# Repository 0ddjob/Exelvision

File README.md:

# Exelvision EXL100
Hardware projects and other info for the French Exelvision EXL100 computer.<br>
It has the following main ICs:
- Texas Instruments TMS4408 ... 8k x 4bit giving 32KBytes of shared VRAM
- NEC D4016 ... 2KByte SRAM for CPU RAM
- Texas Instruments TAL004 ... Gate Array
- Texas Instruments L30002N ... TMS 7220 CPU
- Texas Instruments C34802N ... TMS 7041 peripheral co-processor
- Texas Instruments TMP5220CNL ... TMS 5220 speech synthesiser
- Texas Instruments TMX3556NS ... TMS 3556 video display processor (VDP)

The ROM cartridge connector is a BURNDY PWBH14DER1A-1 which I can't find any info on - it's a 2x14 design.<br>

## YouTube Videos
- [Part 1: First Look](https://youtu.be/5-ew3FQ9LnI)
- [Part 2: Cartridge Pinout](https://youtu.be/ktFMq2L3tBw)
- [Simple Kicad For Simple Vintage Computer Hobbyists: Part 4 (ROM Cartridge Design)](https://youtu.be/4mT13-wXdjI)
- [Part 3: DIY Cartridges](https://youtu.be/ecWkOvze2gc)

## [EXLROM - Multi-ROM cartridge](/EXLROM/)
The EXL100 could accept ROM cartridges from 8KByte to 32KByte in size, including BASIC.  By using a 4Mbit ROM (27C040) we can fit all known ROMs onto one cartridge.  How exciting.<br>
I've designed two versions: a simple 256kbit version that will hold a single 32KByte ROM (like the olden days) and the 4Mbit version that will hold up to 16 32KByte ROMs.<br>
### Status
- 1-Apr-2025:  Pending test fabrication 
- 10-Apr-2025: Test PCBs arrived & verified! Refer YouTube video.

## Partial TAL004 Gate Array Pinout
From cartridge pinout investigation ... <br>

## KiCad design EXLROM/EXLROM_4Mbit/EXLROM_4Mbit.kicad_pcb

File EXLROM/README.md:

# EXLROM Multi-ROM Cartridge
## Summary
The Exelvision EXL100 (and Exeltel) cartridge port pinout is below - the B-side face up and A-side face down when the cartridge is inserted.<br>
The pinout was determined from the 32KByte Tennis cartridge.  The A1 pin was not connected in this cartridge but is connected to pin 40 of the TAL004 gate array ... perhaps a 2nd ROM select line?<br>
```
A1 = ROMCS2(?)  B1 = ROMCS1
A2 = A13        B2 = A14
A3 = A11        B3 = A12
A4 = A9         B4 = A10
A5 = A7         B5 = A8
A6 = A5         B6 = A6
A7 = GND        B7 = A4
A8 = N/C        B8 = +5V
A9 = A3         B9 = A2
A10 = A1        B10 = A0
A11 = D7        B11 = D6
A12 = D5        B12 = D4
A13 = D3        B13 = D2
A14 = D1        B14 = D0
```
## [Simple Single ROM Version](/EXLROM/EXLROM_256Kbit/)
This version takes a 32KByte 27C256 EPROM that will fit a single 32KByte ROM.  The smaller 8KByte and 16KByte ROMs will just have empty space.<br>

## [Multi-ROM](/EXLROM/EXLROM_4Mbit/)
This version should fit all known Exelvision ROMs.<br>

## Bank Selection
Using a 4MBit EPROM allows us to fit 16 32KByte ROMs selectable via four dip switches that determine the value of the A15 to A18 address lines.  A single ROM can be created by concatenating 32KByte ROMs into one file - very simply done in Linux or Windows via command line.  Smaller ROMs (8KByte and 16KByte) can be duplcated (i.e. four concatenated copies of the 8KByte ROM) to bring their size up to 32KBytes.
```
AAAA 
1111
8765 Bank  ROM Address Range
---- ----  -----------------
0000    0  0x00000-0x07FFF
0001    1  0x08000-0x0FFFF
0010    2  0x10000-0x17FFF
0011    3  0x18000-0x1FFFF
0100    4  0x20000-0x27FFF
0101    5  0x28000-0x2FFFF
0110    6  0x30000-0x37FFF
0111    7  0x38000-0x3FFFF
1000    8  0x40000-0x47FFF
1001    9  0x48000-0x4FFFF
1010   10  0x50000-0x57FFF
1011   11  0x58000-0x5FFFF
1100   12  0x60000-0x67FFF
1101   13  0x68000-0x6FFFF
1110   14  0x70000-0x77FFF
1111   15  0x78000-0x7FFFF
```
## Cartridge Pinout
The B-side that faces up when inserted.  Pins are numbered B1 on the right to B14 on left.<br>

The A-side that faces down when inserted.  Pins are numbered A1 on the right and A14 on the left.<br>

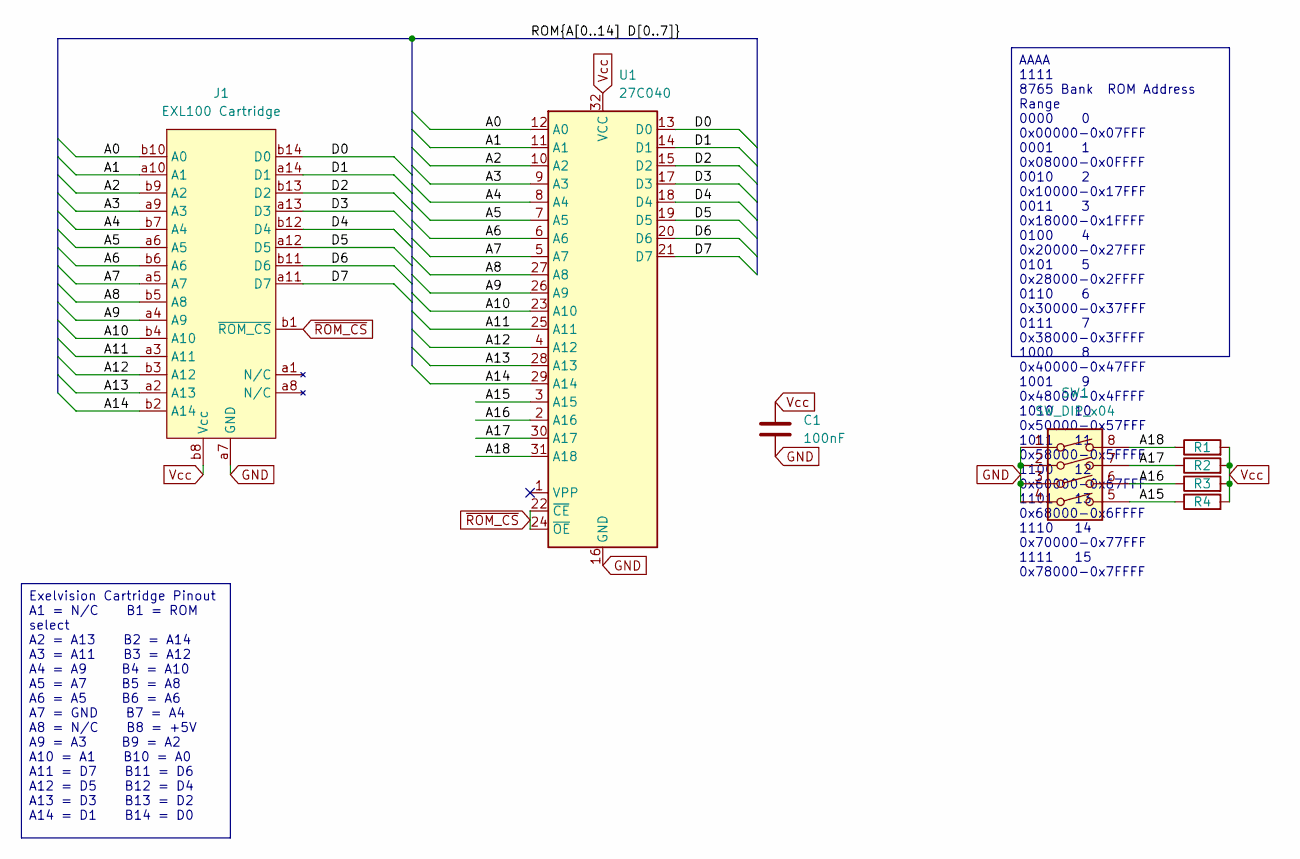
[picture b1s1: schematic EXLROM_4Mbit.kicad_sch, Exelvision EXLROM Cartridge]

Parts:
C1: 100nF; C_Disc_D3.0mm_W2.0mm_P2.50mm
J1: EXL100 Cartridge; EXL100_Cartridge
R1, R2, R3, R4: 10KΩ; R_Axial_DIN0207_L6.3mm_D2.5mm_P10.16mm_Horizontal
SW1: SW_DIP_x04; SW_DIP_SPSTx04_Slide_9.78x12.34mm_W7.62mm_P2.54mm
U1: 27C040; DIP-32_W15.24mm_Socket

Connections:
/A0: J1.b10 (A0), U1.12 (A0)
/A1: J1.a10 (A1), U1.11 (A1)
/A2: J1.b9 (A2), U1.10 (A2)
/A3: J1.a9 (A3), U1.9 (A3)
/A4: J1.b7 (A4), U1.8 (A4)
/A5: J1.a6 (A5), U1.7 (A5)
/A6: J1.b6 (A6), U1.6 (A6)
/A7: J1.a5 (A7), U1.5 (A7)
/A8: J1.b5 (A8), U1.27 (A8)
/A9: J1.a4 (A9), U1.26 (A9)
/A10: J1.b4 (A10), U1.23 (A10)
/A11: J1.a3 (A11), U1.25 (A11)
/A12: J1.b3 (A12), U1.4 (A12)
/A13: J1.a2 (A13), U1.28 (A13)
/A14: J1.b2 (A14), U1.29 (A14)
/A15: R4.1, SW1.5, U1.3 (A15)
/A16: R3.1, SW1.6, U1.2 (A16)
/A17: R2.1, SW1.7, U1.30 (A17)
/A18: R1.1, SW1.8, U1.31 (A18)
/D0: J1.b14 (D0), U1.13 (D0)
/D1: J1.a14 (D1), U1.14 (D1)
/D2: J1.b13 (D2), U1.15 (D2)
/D3: J1.a13 (D3), U1.17 (D3)
/D4: J1.b12 (D4), U1.18 (D4)
/D5: J1.a12 (D5), U1.19 (D5)
/D6: J1.b11 (D6), U1.20 (D6)
/D7: J1.a11 (D7), U1.21 (D7)
GND: C1.2, J1.a7 (GND), SW1.1, SW1.2, SW1.3, SW1.4, U1.16 (GND)
Vcc: C1.1, J1.b8 (Vcc), R1.2, R2.2, R3.2, R4.2, U1.32 (VCC)
~ROM_CS: J1.b1 (~ROM_CS), U1.22 (~CE), U1.24 (~OE)

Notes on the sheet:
Exelvision Cartridge Pinout A1 = N/C B1 = ROM select A2 = A13 B2 = A14 A3 = A11 B3 = A12 A4 = A9 B4 = A10 A5 = A7 B5 = A8 A6 = A5 B6 = A6 A7 = GND B7 = A4 A8 = N/C B8 = +5V A9 = A3 B9 = A2 A10 = A1 B10 = A0 A11 = D7 B11 = D6 A12 = D5 B12 = D4 A13 = D3 B13 = D2 A14 = D1 B14 = D0
AAAA 1111 8765 Bank ROM Address Range 0000 0 0x00000-0x07FFF 0001 1 0x08000-0x0FFFF 0010 2 0x10000-0x17FFF 0011 3 0x18000-0x1FFFF 0100 4 0x20000-0x27FFF 0101 5 0x28000-0x2FFFF 0110 6 0x30000-0x37FFF 0111 7 0x38000-0x3FFFF 1000 8 0x40000-0x47FFF 1001 9 0x48000-0x4FFFF 1010 10 0x50000-0x57FFF 1011 11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

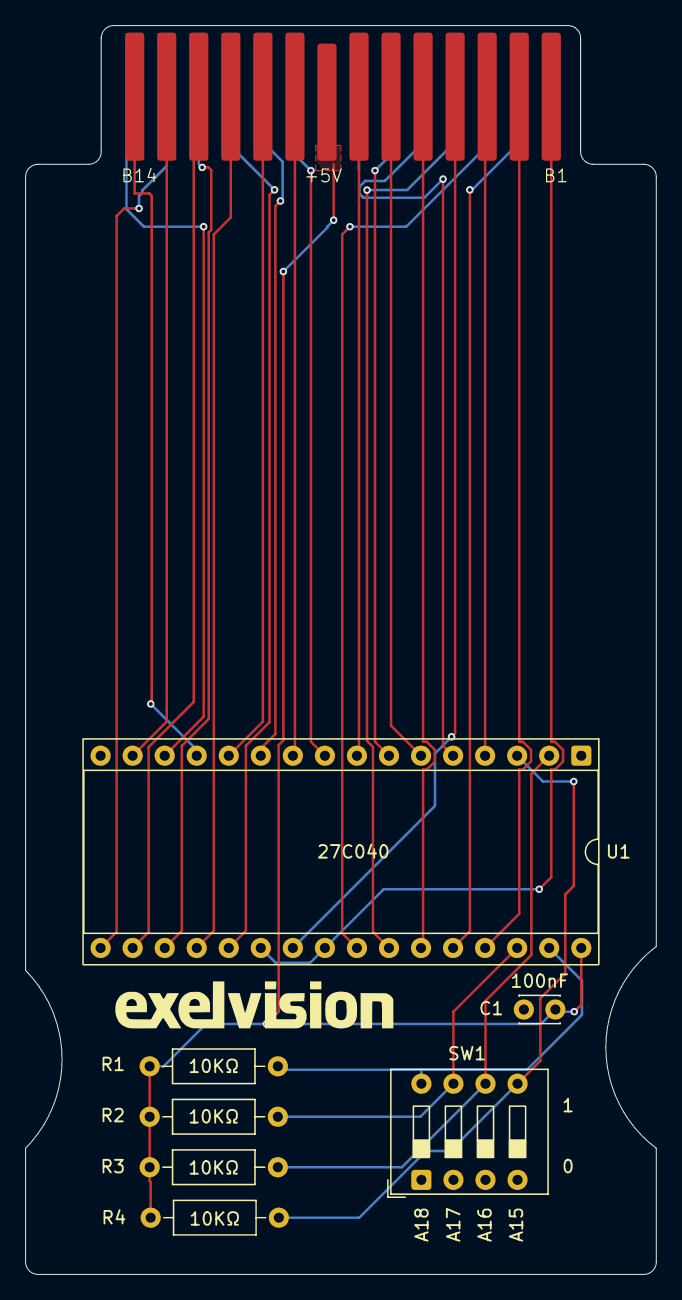
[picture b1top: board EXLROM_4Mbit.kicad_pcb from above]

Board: 2 copper layers, 50.0 x 99.0 mm, 8 parts (0 on the bottom side), 30 nets.

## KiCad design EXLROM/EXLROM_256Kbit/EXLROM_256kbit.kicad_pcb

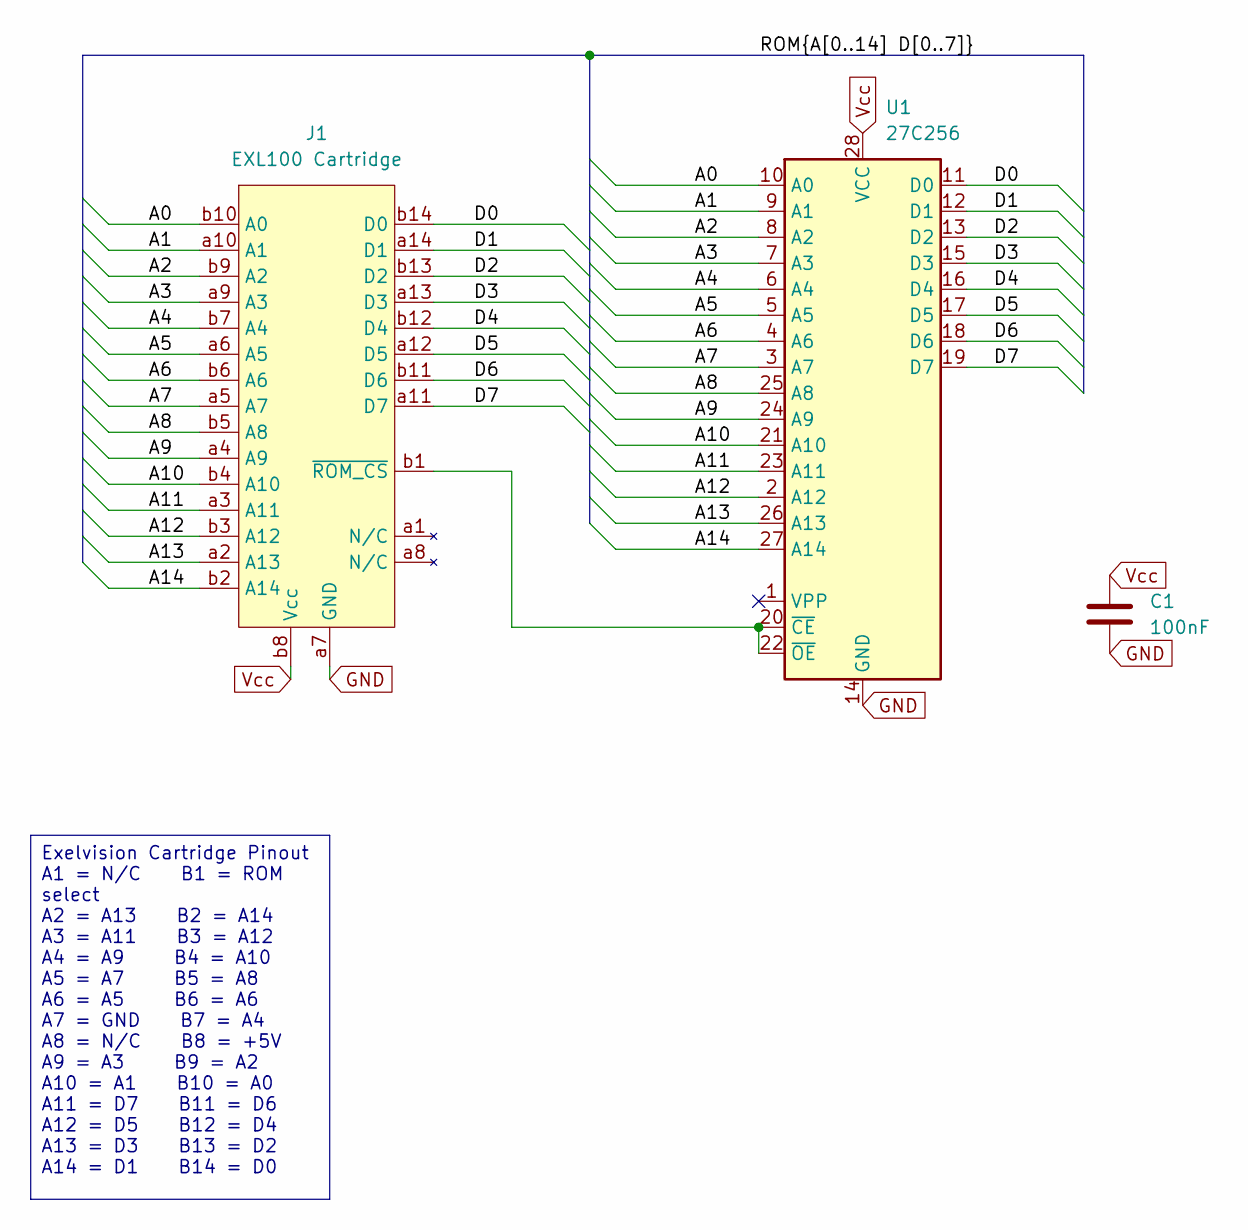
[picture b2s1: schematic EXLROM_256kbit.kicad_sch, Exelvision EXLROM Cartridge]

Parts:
C1: 100nF; C_Disc_D3.0mm_W2.0mm_P2.50mm
J1: EXL100 Cartridge; EXL100_Cartridge
U1: 27C256; DIP-28_W15.24mm

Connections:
/A0: J1.b10 (A0), U1.10 (A0)
/A1: J1.a10 (A1), U1.9 (A1)
/A2: J1.b9 (A2), U1.8 (A2)
/A3: J1.a9 (A3), U1.7 (A3)
/A4: J1.b7 (A4), U1.6 (A4)
/A5: J1.a6 (A5), U1.5 (A5)
/A6: J1.b6 (A6), U1.4 (A6)
/A7: J1.a5 (A7), U1.3 (A7)
/A8: J1.b5 (A8), U1.25 (A8)
/A9: J1.a4 (A9), U1.24 (A9)
/A10: J1.b4 (A10), U1.21 (A10)
/A11: J1.a3 (A11), U1.23 (A11)
/A12: J1.b3 (A12), U1.2 (A12)
/A13: J1.a2 (A13), U1.26 (A13)
/A14: J1.b2 (A14), U1.27 (A14)
/D0: J1.b14 (D0), U1.11 (D0)
/D1: J1.a14 (D1), U1.12 (D1)
/D2: J1.b13 (D2), U1.13 (D2)
/D3: J1.a13 (D3), U1.15 (D3)
/D4: J1.b12 (D4), U1.16 (D4)
/D5: J1.a12 (D5), U1.17 (D5)
/D6: J1.b11 (D6), U1.18 (D6)
/D7: J1.a11 (D7), U1.19 (D7)
GND: C1.2, J1.a7 (GND), U1.14 (GND)
unnamed: J1.b1 (~ROM_CS), U1.20 (~CE), U1.22 (~OE)
Vcc: C1.1, J1.b8 (Vcc), U1.28 (VCC)

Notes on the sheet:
Exelvision Cartridge Pinout A1 = N/C B1 = ROM select A2 = A13 B2 = A14 A3 = A11 B3 = A12 A4 = A9 B4 = A10 A5 = A7 B5 = A8 A6 = A5 B6 = A6 A7 = GND B7 = A4 A8 = N/C B8 = +5V A9 = A3 B9 = A2 A10 = A1 B10 = A0 A11 = D7 B11 = D6 A12 = D5 B12 = D4 A13 = D3 B13 = D2 A14 = D1 B14 = D0

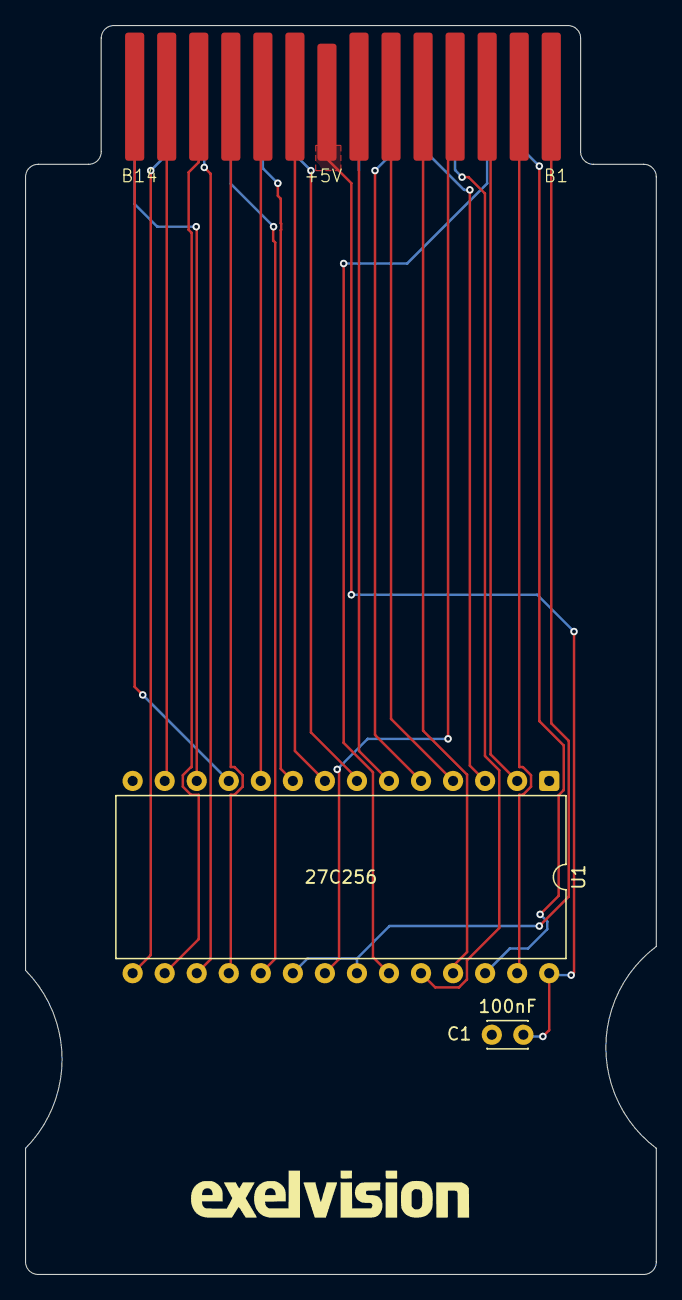
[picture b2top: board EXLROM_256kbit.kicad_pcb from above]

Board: 2 copper layers, 50.0 x 99.0 mm, 3 parts (0 on the bottom side), 26 nets.

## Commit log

2025-04-01 Adjusting folder structure
2025-04-01 Cartridge images
2025-04-01 Added 256kbit version
2025-04-01 PCB silkscreen update
2025-04-10 Added ROMs & corrected silkscreen
2025-04-10 Corrected folder structure
2025-04-10 Cleaning up
2025-04-10 Added additional fabrication-related files
2025-04-10 Smaller image
